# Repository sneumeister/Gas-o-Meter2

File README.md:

[↓ Switch to English](README_EN.md)

# Gas-O-Meter2

ESP32-C6-basiertes Gaszähler-Monitoring mit **LP-Core Pulse-Counting**, akkubetriebenem Deep-Sleep und wählbaren Übertragungswegen (WiFi/MQTT, BLE, Zigbee).

Custom Carrier-PCB mit **TPL5110**-Mikrotimer für saubere Reed-Impulse, optionalem 3D-Druck-Gehäuse und Web-Interface zur Konfiguration.

## Features

- **TPL5110** — entprellt den Reed-Kontakt und liefert ein definiertes Zähler-Signal (~3,5 s); kompensiert den fehlenden Schmitt-Trigger-Eingang am ESP32-C6
- **LP-Core (ULP)** — Pulszählung im Low-Power-Core (`ulp/ulp_main.c`); der HP-Core ist nur bei Wake-up zur Datenübertragung aktiv
- **Deep-Sleep** — konfigurierbares Wake-up-Intervall über `wakeup_minutes` in der Config
- **NVS Ring-Buffer** — Sicherung des Zählerstands nur bei **Low-Akku** (< 30% / < 3,57V); bei Akku ≥ 30% bleibt der Stand im RTC-RAM (auch bei USB/VBUS), um den Flash zu schonen
- **Web-Interface** — Status und Konfiguration über LittleFS (`data/index.html`, `config.html`); im **Dauerbetrieb** (Timer-Wake-up) nicht automatisch erreichbar
- **Taster A** — Web-UI und WiFi nur nach Wake-up über **Taster A** auf der Platine; bei reinem Timer-Wake-up erfolgt nur die Datenübertragung, danach sofort Deep-Sleep
- **Taster B** — derzeit **ohne Funktion**
- **Transfer-Modi** — `none`, `mqtt`, `ble` oder `zigbee` (jeweils ein Modus aktiv)
- **Akku-Laufzeit v1.0.7** — Zigbee (linkquality ~25) ca. 450h

## Hardware

- **MCU:** [Seeed Studio XIAO ESP32-C6](https://wiki.seeedstudio.com/xiao_esp32c6_getting_started/) auf Custom Carrier-PCB
- **Sensorik:** Reed-Schalter für Gaszähler-Impulse, TPL5110, Akku- und USB-Erkennung
- **Dokumentation:**
  - [KiCAD-Platinen](KiCAD-PCB/README.md) — Schaltplan, BOM, 3D-Ansicht und Platinenversionen
  - [Gehäuse / 3D-Druck](CAD-housing/README.md) — STEP-Dateien, Creo-Quellen und Fotos

Die Firmware-Revision (`BOARD_VERSION_ID`, siehe [Build & Flash](#build--flash)) steuert nur die **USB-Erkennung**: Der Default `PCB_20251022` läuft auch auf der neuen Platine (Revision 20260523), nutzt dort aber die ADC-Heuristik statt VBUS an GPIO18. Für die dedizierte VBUS-Erkennung der zweiten Revision: `PCB_20260523`. Details zu den Platinen über die [KiCAD-Übersicht](KiCAD-PCB/README.md).

## Übertragungswege (Transfer-Modi)

| Modus | Beschreibung | Integration |
| ----- | ------------ | ----------- |
| `mqtt` | WiFi + MQTT (+ optional Home Assistant Autodiscovery) | NTP-Zeitsync, `transfer_mqtt.cpp` |
| `ble` | NimBLE, JSON-Notify auf Characteristic 0xFFF1 | [Node-RED Flow](integration_templates/nodered/README.md) |
| `zigbee` | Zigbee End Device (Metering + Battery Cluster) | [Zigbee2MQTT Converter](integration_templates/zigbee2mqtt/README.md) |
| `none` | Nur lokale Erfassung; kein externer Transfer | — |

Einstieg für externe Systeme: [integration_templates/README.md](integration_templates/README.md)

## Akku-Schutz & Wake-up

LiPo-Spannungsreihe (wie in der Firmware hinterlegt; %-Anzeige wird dazwischen linear interpoliert):

| Spannung | % | Ohne USB (Akku) | Mit USB |
| -------- | - | --------------- | ------- |
| ≥ 4,02V | 100% | Normal: Transfer, Zähler im RTC-RAM | Normal: Transfer, Zähler im RTC-RAM (kein NVS) |
| 3,92V | 80% | wie oben | wie oben |
| 3,72V | 50% | wie oben | wie oben |
| 3,57V | 30% | Ab hier bzw. darunter: Low-Battery-Meldung; Zähler in NVS | wie links |
| 3,42V | 20% | Darunter: Sofort Deep-Sleep, **kein** Transfer; Timer weiter bis 3,15V | Schutz greift **nicht** → Transfer wie normal |
| ≤ 3,15V | 0% | Timer aus; nur **Taster A** weckt | Timer bleibt an |

**Zurück in den Normalbetrieb** (Timer war aus): USB allein weckt **nicht**. USB anstecken und **Taster A** drücken (startet Web-UI; warten bis Web-Timeout) — danach Deep-Sleep mit Timer.

**USB-Erkennung nach Platine:**

- **20251022:** USB = gemessene Spannung < 2,0V. Zwischen 2,0V und 3,42V gilt *kein* USB → Akkuschutz greift.
- **20260523:** USB über VBUS-Pin, unabhängig von der Akkuspannung (Firmware-Environment `PCB_20260523`).

Der LP-Core zählt Impulse weiter, solange der Chip versorgt ist. **Taster B** hat aktuell keine Funktion.

## Software-Übersicht

| Komponente | Pfad / Modul | Aufgabe |
| ---------- | ------------ | ------- |
| HP-Core | `src/main_idf.cpp` | Boot, Config, HTTP-Server, ADC, Deep-Sleep, Transfer-Orchestrierung |
| LP-Core | `ulp/ulp_main.c` | Reed-Pulse-Counting auf GPIO2 |
| Transfer | `src/transfer.cpp`, `transfer_{mqtt,ble,zigbee}.cpp` | Modus-Dispatcher und Protokoll-Stacks |
| Netzwerk | `src/wifi_manager.cpp`, `src/time_sync.cpp` | WiFi STA/AP, mDNS, NTP |
| Persistenz | `data/` (LittleFS), `pulse_nv` (NVS) | Web-UI, `config.json`, Zähler-Ringpuffer |
| Version | `include/version.h` | `Gas-O-Meter2` v1.0.7 |

**Typischer Ablauf:** TPL5110 weckt ESP → LP-Core liefert Zählerstand → HP-Core liest ADC/Config → optional Transfer → Deep-Sleep.

## Entwicklungsumgebung

| Komponente | Version / Quelle |
| ---------- | ---------------- |
| IDE | VS Code oder **Cursor** mit PlatformIO-Extension |
| PlatformIO | [pioarduino/platform-espressif32](https://github.com/pioarduino/platform-espressif32) (stable zip in `platformio.ini`) |
| Framework | **ESP-IDF 5.5.1** (`sdkconfig.defaults`) |
| Board | `seeed_xiao_esp32c6` |
| Extension (empfohlen) | `pioarduino.pioarduino-ide` + `vscode-clangd` (`.vscode/extensions.json`, `gas-o-meter2.code-workspace`) |
| IntelliSense | `clangd` (`.vscode/settings.json`; Espressif-clangd setzt pioarduino lokal) |

**Voraussetzungen:** PlatformIO CLI, Git, USB-Treiber für XIAO ESP32-C6.

## Build & Flash

Standard-Environment in [`platformio.ini`](platformio.ini): `PCB_20251022`

| Environment | USB-Erkennung | Befehl |
| ----------- | ------------- | ------ |
| `PCB_20251022` | ADC-Heuristik (Default; läuft auf beiden Platinenrevisionen) | `pio run` / `pio run -t upload` |
| `PCB_20260523` | VBUS an GPIO18 (nur sinnvoll auf Revision 20260523) | `pio run -e PCB_20260523 -t upload` |
| `TPL_test` | — (Hardwaretest TPL5110/Reed an GPIO2, ohne LP-Core/WiFi) | `pio run -e TPL_test -t upload` |

**TPL_test:** Seriell `pio device monitor -e TPL_test` (115200). Monitor **vor** dem Reset öffnen oder Board danach neu starten (USB-CDC). Flanken auf GPIO2 mit µs-Zeitstempel und Intervall `dt`; alle 2 s ein Heartbeat. **Funktionstest TPL:** Reed kurz tippen → ein LOW ~3–4 s, dann HIGH; Reed dauerhaft brücken → nur **ein** LOW, das bis zum Öffnen der Brücke anhält (keine kurzen HIGH-Lücken dazwischen). **Magnettest:** Reed-Schalter mit Magnet auslösen (typische Empfindlichkeit/Abstand). Details: [`src/main_TPL_test.cpp`](src/main_TPL_test.cpp).

`BOARD_VERSION_ID` steuert in `include/hardware.h`, ob USB per ADC-Schwellwert oder per VBUS-GPIO erkannt wird — kein harter Platinen-Zwang.

**Erstinstallation:**

1. Repository klonen
2. `data/config.json` aus [`data/config.json_example`](data/config.json_example) erstellen
3. Firmware flashen: `pio run -t upload` (Default); optional `-e PCB_20260523` für VBUS-Erkennung auf Revision 20260523
4. Filesystem flashen: `pio run -t uploadfs` (Web-UI und Default-Config)
5. Seriell monitorieren: `pio device monitor` (115200 baud)

**Partitionen** (`partitions.csv`): Factory-App, `pulse_nv` (NVS-Ring), Zigbee-Speicher, LittleFS.

### Web-Flash und Releases

Ohne PlatformIO kann die Firmware über den
[Gas-O-Meter2 Web-Flasher](https://sneumeister.github.io/Gas-o-Meter2/)
installiert werden (Firefox ab Version 151 auf Desktop-Systemen, Chrome oder
Edge; USB-Datenkabel erforderlich). Firefox installiert beim ersten Zugriff
eine seitenspezifische Berechtigungs-Erweiterung; eine zusätzliche
Drittanbieter-Erweiterung ist nicht notwendig. Unterstützt werden beide
PCB-Versionen sowie `TPL_test`.

- **Complete:** Erstinstallation oder ein in den Release Notes als
  **Breaking** markiertes Update; PCB-Complete setzt persistente Konfiguration
  und Zähler-/Zigbee-Daten zurück
- **Firmware:** nur Programmcode
- **LittleFS:** nur Web-UI und Default-Konfiguration; überschreibt die aktuelle
  Gerätekonfiguration

Bei Firmware-/LittleFS-Teilupdates im ESP-Web-Tools-Dialog niemals
**„Erase device“** wählen.

Release-Tags `v*` bauen und veröffentlichen diese Dateien automatisch. Die
Maintainer-Schritte stehen in [RELEASING.md](RELEASING.md).

## Konfiguration

Zwei Wege:

1. **Web-UI** nach Wake-up über **Taster A** ([Anleitung zur Web-UI](README_WEBUI.md))
2. `data/config.json` — manuell oder über die Web-UI speichern

**Hinweis Dauerbetrieb:** Bei periodischem Timer-Wake-up (Akku-Betrieb) wacht das Gerät nur kurz auf, überträgt ggf. Daten und geht wieder in Deep-Sleep — **ohne** Web-Frontend. Status und Konfiguration sind nur nach manuellem Wake-up über **Taster A** erreichbar (WiFi STA oder Captive Portal im AP-Modus).

Wichtige Config-Keys (vollständig in `config.json_example`):

| Gruppe | Keys |
| ------ | ---- |
| Gerät | `hostname`, `adminpass` |
| WiFi | `wifiCredentials` (max. 2 Netze) |
| Timing | `wakeup_minutes`, `transfer_interval_x` |
| Transfer | `transfer_mode` (`none` / `mqtt` / `ble` / `zigbee`) |
| MQTT | `mqtt_host`, `mqtt_port`, `mqtt_username`, `mqtt_password`, `mqtt_main_topic`, `mqtt_ha_autodiscovery`, `ntp_server` |
| Kalibrierung / TX | `adc_voltage_multiplier`, `wifi_tx_power_dbm`, `ble_tx_power_dbm`, `zigbee_tx_power_dbm` |

## Projektstruktur

```text
gas-o-meter2/
├── src/                    # Firmware (ESP-IDF)
├── ulp/                    # LP-Core Pulse-Counting
├── data/                   # LittleFS Web-UI + config.json
├── include/                # Header (hardware, transfer, version)
├── KiCAD-PCB/              # Platinen-Dokumentation
├── CAD-housing/            # Gehäuse STEP/Creo/Bilder
├── integration_templates/  # Zigbee2MQTT, Node-RED
├── pictures/webui/         # Screenshots für README_WEBUI.md
├── scripts/                # Release-Build und Artefakt-Verifikation
├── web-flasher/            # GitHub-Pages-Installseite (ohne Binaries)
├── RELEASING.md            # Maintainer-Anleitung für Releases
└── platformio.ini          # Build-Environments
```

## Lizenz

Gas-O-Meter2 ist unter der [Apache License 2.0](./LICENSE) veröffentlicht.
Copyright- und Attributionshinweise stehen in [`NOTICE`](./NOTICE). Die
Lizenzen der verwendeten Bibliotheken dokumentiert
[`THIRD_PARTY_NOTICES.md`](./THIRD_PARTY_NOTICES.md).

Die permissive Apache-2.0-Lizenz wurde gewählt, um mögliche Konflikte zwischen
starkem Copyleft und den zusätzlichen Binärbedingungen der separat
lizenzierten ZBOSS-Komponente zu vermeiden. ZBOSS und alle weiteren
Drittanbieter-Komponenten behalten ihre jeweils eigene Lizenz.

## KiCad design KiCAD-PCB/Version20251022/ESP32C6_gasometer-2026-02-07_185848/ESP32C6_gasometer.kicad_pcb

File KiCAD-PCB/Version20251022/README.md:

[↓ Switch to English](README_EN.md)

# Gas-O-Meter2 — Platinenversion 20251022

KiCAD-Projekt und Stückliste (BOM) der ersten Platinenrevision.

- Akku-Spannung am **GPIO0** (Pin1/A0/D0) mittels **1:1-Spannungsteiler** (R2/R3)
- **USB-Spannungsversorgung** durch **ADC-Heuristik** (Batteriespannung unter 2,0 V; kein VBUS-Pin)

## Schaltplan

[ESP32C6_gasometer (PDF)](ESP32C6_gasometer.pdf)

## Stückliste (BOM)

Quelle: `BOM_ESP32C6_gasometer.xlsx`

| Reference | Qty | Beschreibung | Value | Datasheet |
| --------- | --- | ------------ | ----- | --------- |
| J1 | 1 | Generic connector, single row, 01x02 // Reed | JST-XH 1.25 2pin socket | |
| J2 | 1 | Generic connector, single row, 01x02 // Reed | JST-XH 1.25 2pin plug | |
| R1 | 1 | Resistor_SMD1206 | 8,2k | |
| R2,R3 | 2 | Resistor_SMD1206 | 220k | |
| SW1 | 1 | reed switch | KSK-1A87-1520 | [Datasheet](https://standexdetect.de/wp-content/uploads/sites/8/2025/09/datasheet-reed-switch-series-ksk-1a80.pdf) |
| SW2,SW3 | 2 | Push button switch, generic, two pins | OMRON_B3F-6000 | [Datasheet](https://omronfs.omron.com/en_US/ecb/products/pdf/en-b3f.pdf) |
| U1 | 1 | Timer, Nano Power, SOT-23-6 | TPL5110 | [Datasheet](http://www.ti.com/lit/ds/symlink/tpl5110.pdf) |
| U2 | 1 | | Seeed Studio XIAO ESP32-C6 | |
| J3 | 1 | Generic connector, single row, 01x02 // Batterie | JST-PH 2.00 2pin socket | |
| | 1 | Li-Polymer Battery 52x34x5,0mm | LiPo 1000mAh 523450 | |

## 3D-Ansicht

## KiCAD-Export

Aktueller Stand: [ESP32C6_gasometer-2026-02-07_185848](ESP32C6_gasometer-2026-02-07_185848/)

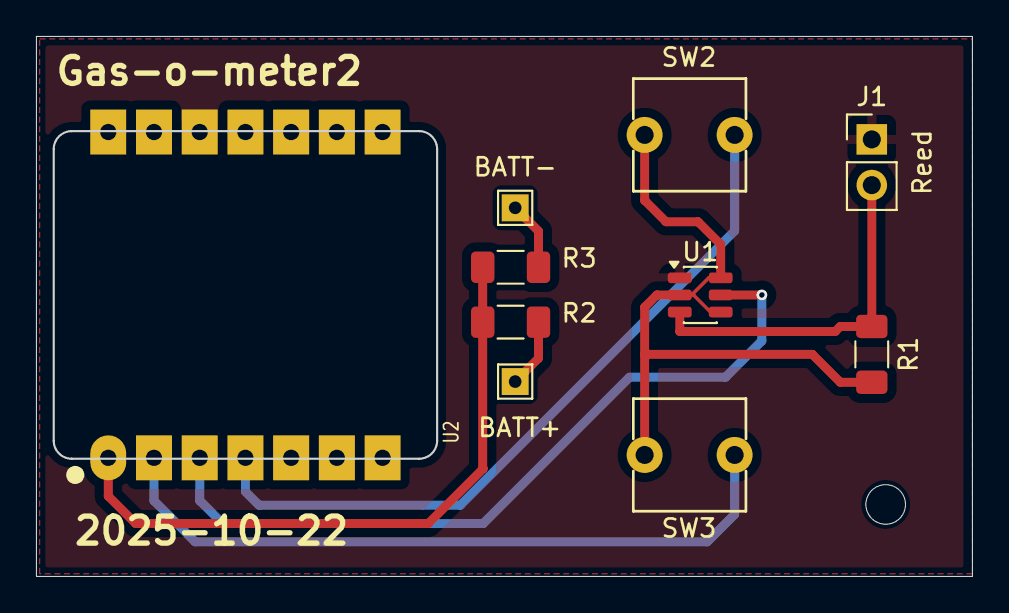
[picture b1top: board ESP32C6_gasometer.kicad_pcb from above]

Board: 2 copper layers, 52.0 x 30.0 mm, 11 parts (0 on the bottom side), 9 nets.

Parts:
.: M.Hole_2.2mm_M2; MountingHole_2.2mm_M2
J1: Reed; PinHeader_1x02_P2.54mm_Vertical
R1: 8,2k; R_1206_3216Metric_Pad1.30x1.75mm_HandSolder
R2, R3: 200k; R_1206_3216Metric_Pad1.30x1.75mm_HandSolder
SW2, SW3: SW_Push; SW_TH_Tactile_Omron_B3F-6000
TP1: BATT+; TestPoint_THTPad_1.5x1.5mm_Drill0.7mm
TP2: BATT-; TestPoint_THTPad_1.5x1.5mm_Drill0.7mm
U1: TPL5110; SOT-23-6
U2: XIAO-ESP32-C6; XIAO-ESP32C6-Breakout

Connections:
+3.3V: J1.1, U1.1 (VDD), U2.12 (3V3)
GND: R1.2, SW2.1, SW3.1, U1.2 (GND), U1.4 (DONE), U1.6 (EN/ONE_SHOT), U2.13 (GND)
unnamed: J1.2, R1.1, U1.3 (DELAY/M_DRV)
unnamed: R2.1, TP1.1
unnamed: R3.2, TP2.1
unnamed: U1.5 (DRV), U2.3 (GPIO2/A2/D2)
unnamed: R2.2, R3.1, U2.1 (GPIO0/A0/D0)
unnamed: SW3.2, U2.2 (GPIO1/A1/D1)
unnamed: SW2.2, U2.4 (GPIO21/D3)

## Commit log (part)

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2025-12-26 Initial commit: Gas-O-Meter2 Projekt
2025-12-28 Neue Logik zum ausliefern Web-Server-Inhalte vom LittleFS. Neuer processor() für Variablenersetzung im HTML (ESPAsynWebserver) und entsprechend die Variablem ESCapes im HTML angepasst (%var%). Basic-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
2025-12-30 Deep-Sleep: Timer-Wake-up bei USB-Stromversorgung aktiv, Akku-Schutz-Logik angepasst Transfer-Intervall: Datenübertragung nur alle X Timer-Wake-ups (DEFAULT_TRANSFER_INTERVAL_X) WiFi: Credentials als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
2025-12-30 Änderungen: Konfigmenü, PLACEHOLDER Neu: data/config.html ==> Konfigurationsmenü Neu: data/config.js ==> Konfigurationsmenü Geändert: data/index.html ==> PLACEHOLDER für Variablen ersetzt Geändert: i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
2026-01-01 Access Point Modus und mobile UI-Optimierungen
    - Access Point Modus bei fehlgeschlagener WiFi-Verbindung (AP IP: 10.0.0.1)
    - NVS-Partition auf 40 KB erhöht für zukünftige Protokolle (BLE, ZigBee)
    - Mobile UI: Responsive Counter-Korrektur, Button-Positionierungen angepasst
    - Config-Seite: Labels in Fettschrift, Buttons näher am Counter-Display
2026-01-06 Erste Version komplett in ESPIDF inklusive LP-Core Code
2026-01-07 Fix: Ring-Speicher-Handling nach Power-Up! Changes to be committed: - modified: src/main_arduino.cpp - modified: src/main_idf.cpp
2026-01-10 Fix: littlefs partition ins partitions.csv muss am Ende stehen, sonst klappt der build nicht! Offensichtlich wird die Größe der letzten Partition als littlefs-Part.Größe genommen! Ausserdem jetzt kon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
2026-01-22 Fix: Gas-Zähler-Reset und NVS-Persistenz verbessert
    - CurrentSummationDelivered VOR Rejoin initialisieren (verhindert Reset auf 0)
    - NVS-Flash-Schreibung: 100ms Delay nach nvs_commit(), 500ms nach zigbee_config_save_to_nvs()
    - NVS-Verifikation erweitert: prüft jetzt auch extended_addr, zusätzliches 50ms Delay vor Verifikation
    - Gesamt-Delay für Flash-Schreibvorgang: 600ms (100ms + 500ms)
    - DeepSleep button in Index.html
    Changes to be committed:
2026-01-25 Fix: Interview-Fehler behoben + Battery-Icon + Optimierungen
    - Fix: device_announce wird jetzt explizit nach Pairing gesendet (Interview-Fix)
    - Fix: Battery-Icon in Zigbee2MQTT (persistente power_source Variable + meta)
    - Fix: Battery-Spannung wird nach Config-Load neu berechnet (korrekter Offset)
    - Erhöhte Join/Steering Retry-Counts und Timeouts für schwache Netzwerke
    - Explizite Battery Reporting-Konfiguration im Converter (1h Fallback)
    - Entfernt: 2s Wartezeit nach Wake-Up, verbose Template-Logs
2026-02-18 Funktionierende ZigBee-Version mit manuellen send der Attribute. Fallbackversion. v0.8.0
2026-03-09 BLE: ESP32C6 NimBLE GATT Server Implementierung
    Vollständige BLE-Datenübertragung für den ESP32C6 mit NimBLE-Stack:
    - include/ble_config.h: BLE-Konfiguration (UUIDs, Timeouts, Advertising)
    - CTS (0x1805), DIS (0x180A), Custom Service (0xFFF0/0xFFF1)
    - Advertising: 90s Dauer, 100ms Intervall, 3min Session-Timeout
    - include/transfer_ble.h + src/transfer_ble.cpp: NimBLE GATT Server
    - Custom Characteristic (0xFFF1): Messdaten als JSON (Read/Notify)
2026-03-18 TX-Power für WiFi, Zigbee und BLE im UI konfigurierbar. UI Optik angepasst. Erreichbarkeit für Transfer-Mode-Settings robuster getsaltet.
    On branch main
    Changes to be committed:
    modified: data/config.html
    modified: data/config.js
    modified: data/config.json_example
    modified: data/style.css
2026-05-09 BLE-Mac-Adresse auf Config.html Seite.
    On branch main
    Changes to be committed:
    modified: data/config.html
    modified: gas-o-meter2.code-workspace
    modified: include/version.h
    modified: src/main_idf.cpp
2026-05-13 fix(z2m): configure ohne falschen logger; cfgLog über console, configureKey 4
    On branch zigbee_reporting_fix
    Changes to be committed:
    modified: integration_templates/zigbee2mqtt/external_converters/gas-o-meter2.js
2026-05-16 Zigbee: Cluster-RAM vor Endpoint mit echten Messwerten befüllen
    Neue Funktion transfer_zigbee_prepare_cluster_attrs() setzt Gas- und
    Battery-Variablen, auf die die ZCL-Attribute zeigen, noch vor
    transfer_zigbee_init() / esp_zb_device_register(). Damit liefert
    create_gas_meter_endpoint() und der erste Z2M-Read nach Join keine
    Defaults mehr (Summation 0, Batterie 4,0 V).
    - transfer_data(): prepare vor init aufrufen
2026-05-16 fix(zigbee): send_data set_attribute_val einmal, Reports unter Lock (TZ-292)
    transfer_zigbee_send_data() ruft prepare_cluster_attrs nur noch einmal auf
    und setzt Metering/Battery mit set_attribute_val erst nach ensure_joined in
    einem [3/4]-Block. Der frühere Block vor ensure_joined und die getrennten
    Schritte [2.5/4]/[3/4] entfallen – Mehrfachaufrufe konnten ungeplante Reports
    auslösen.
    Explizite Attribute-Reports laufen gebündelt unter esp_zb_lock_acquire via
2026-05-16 fix(zigbee): SummationFormatting 0x2A für 2 Nachkommastellen (Divisor 100)
    summation_formatting=0 bedeutete keine Dezimalstellen; ZCL-Clients können
    den Zählerstand falsch darstellen. 0x2A = 5 Vorkommastellen, 2 Nachkommastellen.
    On branch zigbee_improvements
    Changes to be committed:
    modified: include/zigbee_config.h
    modified: src/transfer_zigbee.cpp
2026-05-16 feat(zigbee): Diagnostics-Cluster mit Last LQI/RSSI für Z2M
    Zigbee2MQTT kann Linkqualität in der Geräteübersicht anzeigen.
    LQI/RSSI kommen aus der Parent-Zeile der Neighbor Table und werden
    bei Join, Rejoin und send_data aktualisiert.
    On branch zigbee_improvements
    Changes to be committed:
    modified: include/transfer_zigbee.h
2026-05-17 fix(zigbee): Stack-APIs für RTC und Diagnostics mit esp_zb_lock absichern
    zigbee_update_rtc_from_stack und Parent-Diagnostics laufen nur noch aus
    dem Application-Task unter Lock; Signal-Handler nutzen _impl ohne Lock.
    On branch zigbee_improvements
    Changes to be committed:
    modified: src/transfer_zigbee.cpp
2026-05-17 refactor(zigbee): set_attribute_val in send_data entfernt (TZ-292)
    Werte liegen in gebundenem Cluster-RAM via prepare_cluster_attrs;
    Belt-and-Braces nur noch über explizite report_attr_cmd_req.
    On branch zigbee_improvements
    Changes to be committed:
    modified: src/transfer_zigbee.cpp
2026-05-17 fix(zigbee): NVS-Save-Retry bei deferred Speichern aus Signal-Handler
    zigbee_nvs_save_pending erst nach erfolgreichem zigbee_config_save_to_nvs()
    zuruecksetzen, damit transiente Flash-Fehler im Main-Loop erneut versucht werden.
    vTaskDelay(500) im Erfolgsfall entfernt – Main-Loop soll nicht blockieren.
    On branch zigbee_improvements
    Changes to be committed:
    modified: src/transfer_zigbee.cpp
2026-05-17 fix(z2m): Batteriespannung im External Converter in Volt statt mV
    Home Assistant erwartet Spannung typischerweise in V (device_class voltage).
    Zigbee liefert weiterhin 100-mV-Einheiten; der Konverter rechnet mit /10 um.
    On branch zigbee_improvements
    Changes to be committed:
    modified: integration_templates/zigbee2mqtt/external_converters/gas-o-meter2.js
2026-05-17 perf(zigbee): passive Rejoin-Wartezeit von 2s auf 300ms reduzieren
    On branch zigbee_improvements
    Changes to be committed:
    modified: include/zigbee_config.h
2026-05-17 fix(zigbee): ungültigen Secondary-Channel-Mask-Aufruf entfernen
    esp_zb_set_secondary_network_channel_set(0) liefert ESP_ERR_INVALID_ARG;
    für direkten Rejoin und Mask-Restore reicht die Primary-Maske.
    On branch zigbee_improvements
    Changes to be committed:
    modified: src/transfer_zigbee.cpp
2026-05-18 fix(zigbee): Underflow bei DEVICE_REBOOT-Poll im direkten Rejoin vermeiden
    remaining_ms vor zigbee_poll_joined_after_reboot() sicher aus timeout_ms
    berechnen; verhindert Unsigned-Underflow und endloses Warten bei spätem
    DEVICE_REBOOT nach INIT-Timeout.
    On branch zigbee_improvements
    Changes to be committed:
    modified: src/transfer_zigbee.cpp
2026-05-18 fix(zigbee): Rejoin-Fehlerpfad RX aus und Broadcast-PAN vom direkten Rejoin ausschließen
    Nach fehlgeschlagenem Rejoin rx_on_when_idle wieder deaktivieren (Sleepy ED).
    ZIGBEE_RTC_HAS_DIRECT_REJOIN_CTX lehnt PAN 0xFFFF ab, um sinnlosen INIT-Timeout zu vermeiden.
    On branch zigbee_improvements
    Changes to be committed:
    modified: include/zigbee_config.h
    modified: src/transfer_zigbee.cpp
2026-05-21 docs(zigbee): transfer_zigbee_deinit dokumentiert Main-Loop-Stopp statt Stack-Teardown
    On branch main
    Changes to be committed:
    modified: include/transfer_zigbee.h
    modified: src/transfer_zigbee.cpp
2026-05-22 fix(mqtt): HA unique_id an Discovery-Object-ID (gas_o_meter2_<slug>_<tail>) angleichen
2026-05-23 PCB Schaltplan Version "20251022" zugefügt
2026-05-24 fix(ha): RSSI als entity_category diagnostic in MQTT-Discovery
    RSSI in transfer_mqtt.cpp und im Node-RED BLE-Flow mit
    entity_category: diagnostic versehen — analog zu Firmware und NTP.
    Ohne Kategorie erschien RSSI als Primärentität in der HA-Geräteübersicht.
    On branch mqtt_improvements
    Changes to be committed:
    modified: integration_templates/nodered/gas-o-meter2-ble-flow.json
2026-05-25 fix(.gitignore): ".claude" von git ausgeschlossen
2026-05-27 fix(mqtt): HA Auto-Discovery reparieren und Availability für Deep Sleep
    Home Assistant hat Discovery-Payloads wegen ungültigem JSON ignoriert
    (Doppelkomma vor availability, fehlendes Komma vor device). Zusätzlich
    verhinderte status=offline (retain) nach jedem Sendezyklus dauerhaft
    „nicht verfügbar“.
    - Discovery-JSON: avail/device-Kommas korrigiert, Payload-Puffer 1536 B
    - HA-Topic-Slug: Bindestriche → Unterstriche (eindeutige object_id)
2026-05-28 chore: esp_lifflefs Kommentare bereinigt.
    Changes to be committed:
    modified: CMakeLists.txt
2026-05-28 Links zu Unter-README.md's zugefügt.
    On branch main
    Changes to be committed:
    modified: integration_templates/README.md
2026-06-04 fix(config): MQTT-Test POST, Transfer-Panel nach Save und Passwort-Toggle
    Transfer-Actions senden urlencoded statt multipart (512-Byte-Limit).
    Nach Config-Save bleibt die Modus-Sektion sichtbar; MQTT-Passwort
    bekommt das Auge wie bei WiFi.
    On branch refract_web_endpoints
    Changes to be committed:
    modified: data/config.html
2026-06-04 fix(config): ZigBee-Status-Fetch gegen veraltete Antworten absichern
    zigbeeStatusFetchSeq: Nur die neueste /zigbee/status-Antwort aktualisiert
    die Tabelle (updateZigbeeStatus und Pairing-Polling).
    Nach Factory-Reset nur noch ein Status-Refresh nach 800 ms statt
    zwei paralleler Fetches, die sich gegenseitig mit alten Daten
    überschreiben konnten.
    On branch refract_web_endpoints
2026-06-04 fix(zigbee): NVS-Sync bei /zigbee/status nur anfordern, nicht sofort schreiben
    Veraltetes zigbee_rtc: RTC aus Stack + pending setzen, Flush in Main-Loop.
    Vermeidet wiederholtes NVS aus dem HTTP-Handler (Wear); Deinit flusht weiter synchron.
    On branch refract_web_endpoints
    Changes to be committed:
    modified: include/transfer_zigbee.h
    modified: src/transfer_zigbee.cpp

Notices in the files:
README.md:
License: Apache 2.0
